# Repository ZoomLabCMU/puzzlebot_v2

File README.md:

# Configuration Control for Physical Coupling of Heterogeneous Robot Swarms
Sha Yi, Zeynep Temel, Katia Sycara

In this repo, we include the hardware design files and the code for our PuzzleBot configuration control project. This is based on the [original PuzzleBot repo](https://github.com/ZoomLab-CMU/puzzlebot). For more videos, please view [this](https://www.youtube.com/watch?v=vOY5iG4dra8). If you find our work useful, please consider citing our paper:  
```
@inproceedings{yi2022configuration,
  title={Configuration Control for Physical Coupling of Heterogeneous Robot Swarms},
  author={Yi, Sha and Temel, Zeynep and Sycara, Katia},
  booktitle={2022 IEEE International Conference on Robotics and Automation (ICRA)},
  year={2022},
  organization={IEEE}
}
```

## Preparation
### Hardware Setup
The hardware setup is the same as in the original [PuzzleBot setup](https://github.com/ZoomLab-CMU/puzzlebot). CAD files and circuit design files can be found in `files/`. The code for the circuit is `hardware_code/wifitcp_motor_only.ino`. Please modify the Wifi settings as [this](https://github.com/ZoomLab-CMU/puzzlebot).

### Software Setup
#### Simulation
Our simulation environment is based on [CoppeliaSim](https://www.coppeliarobotics.com/). The physics engine used is [Vortex Studio](https://www.cm-labs.com/vortex-studio/). Both the simulation and physics engine is free for educational use.  

Note that `Bullet` and `ODE` does not work for our concave robot body and will cause instability during contacts.  

Install the [ROS interface](https://www.coppeliarobotics.com/helpFiles/en/ros1Tutorial.htm) for _CoppeliaSim_.  

#### Packages
Basic ROS knowledge is required to run the demo. To build the ROS package, copy the repo into your ROS catkin source directory and build the package.

## Run the Demo in Simulation
1. Start `roscore`. Make sure the package is built in your catkin source directory.
2. Launch _CoppeliaSim_. Note that this should be ran after `roscore` to enable the ROS interface of the simulator.
3. Open the example simulation environment in `simulation/random_4.ttt`. Double check the _Vortex Studio_ is running properly.
4. Run the demo provided with 
```
rosrun puzzlebot_control run.py [NUMBER_OF_ROBOTS]
```
Note that if you would like to run different number of robots, you may also need to modify the target configuration parameters in [`src/puzzlebot_control/controller.py#L266`](src/puzzlebot_control/controller.py#L266).

## Run the Demo on Hardware Platform
Please follow the same procedure as in [this](https://github.com/ZoomLab-CMU/puzzlebot).

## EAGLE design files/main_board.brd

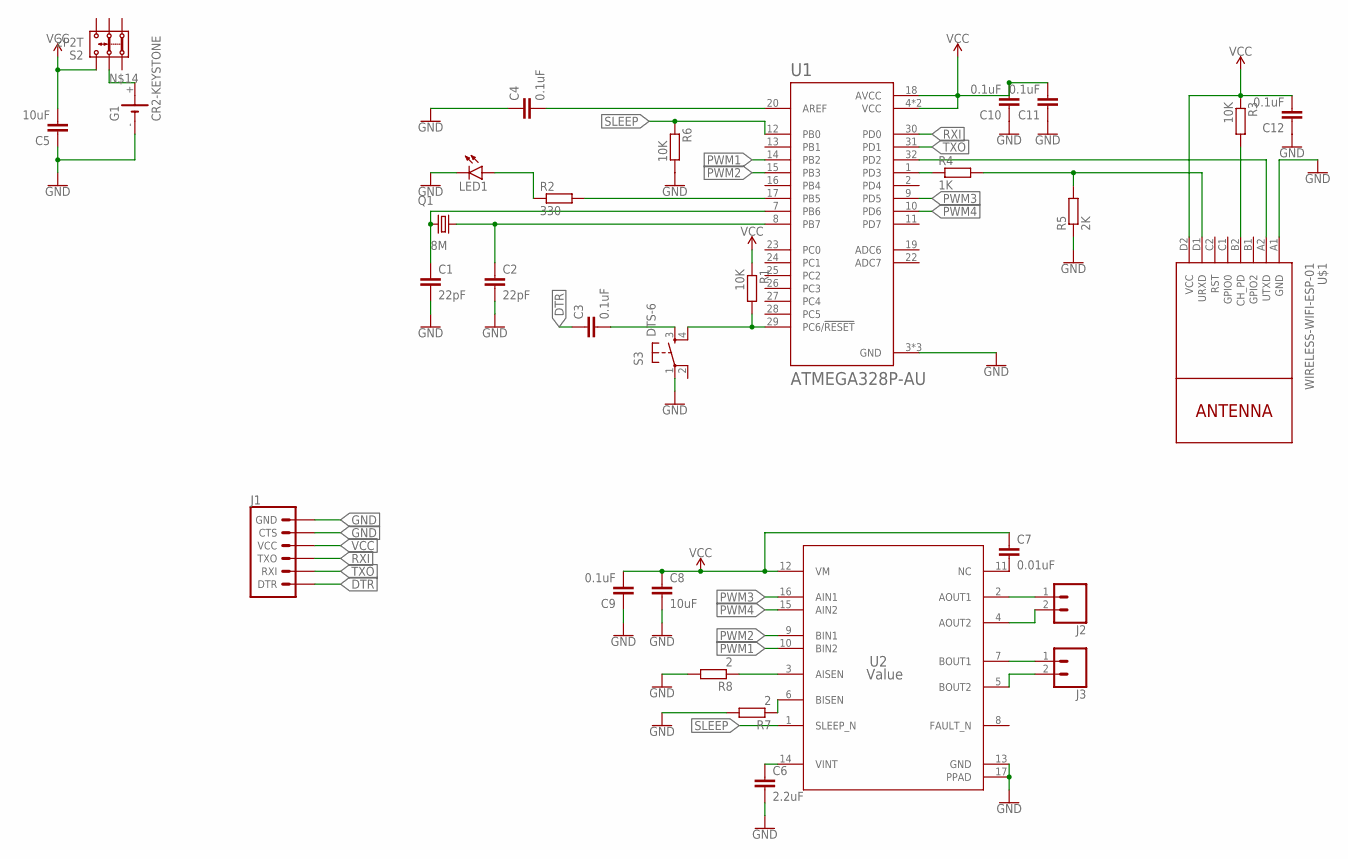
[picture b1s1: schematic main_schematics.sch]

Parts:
C1, C2: 22pF; C0603
C3, C4, C9, C10, C11, C12: 0.1uF; C0603
C5, C8: 10uF; C0603
C6: 2.2uF; C0603
C7: 0.01uF; C0603
G1: CR2-KEYSTONE; SL-150-1/2AA/PR
J1: 6_PIN_SERIAL_TARGETLONGPADS; 1X06_LONGPADS
J2, J3: CONN_02POLAR; MOLEX-1X2
LED1: LEDCHIP-LED0805; CHIP-LED0805
Q1: 8M; CSM-7X-DU
R1, R3, R6: 10K; R0603
R2: 330; R0603
R4: 1K; R0603
R5: 2K; R0603
R7, R8: 2; R0603
S2: 2P2T
S3: DTS-6
U1: ATMEGA328P-AU; QFP80P900X900X120-32N
U2: Value; PWP0016K_M
U$1: WIRELESS-WIFI-ESP-01

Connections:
DTR: C3.1, J1.1 (DTR)
GND: C1.2, C2.2, C4.1, C5.1, C6.2, C8.2, C9.1, C10.1, C11.1, C12.1, G1.-, J1.5 (CTS), J1.6 (GND), LED1.C, R5.1, R6.2, R7.2, R8.2, S3.1, U1.3 (GND), U1.5 (GND), U1.21 (GND), U2.13 (GND), U2.17 (PPAD), U$1.A1 (GND)
unnamed: C2.1, Q1.2, U1.8 (PB7)
unnamed: C1.1, Q1.1, U1.7 (PB6)
unnamed: C3.2, S3.3
unnamed: R1.2, S3.4, U1.29 (PC6/!RESET)
unnamed: R3.2, U$1.B2 (CH_PD)
unnamed: R2.2, U1.17 (PB5)
unnamed: LED1.A, R2.1
unnamed: C4.2, U1.20 (AREF)
unnamed: U1.32 (PD2), U$1.A2 (UTXD)
unnamed: R4.1, U1.1 (PD3)
unnamed: R4.2, R5.2, U$1.D1 (URXD)
unnamed: C6.1, U2.14 (VINT)
unnamed: C7.2, U2.11 (NC)
unnamed: G1.+, S2.2.1
unnamed: R7.1, U2.6 (BISEN)
unnamed: R8.1, U2.3 (AISEN)
unnamed: J2.1, U2.2 (AOUT1)
unnamed: J3.1, U2.7 (BOUT1)
unnamed: J2.2, U2.4 (AOUT2)
unnamed: J3.2, U2.5 (BOUT2)
PWM1: U1.14 (PB2), U2.10 (BIN2)
PWM2: U1.15 (PB3), U2.9 (BIN1)
PWM3: U1.9 (PD5), U2.16 (AIN1)
PWM4: U1.10 (PD6), U2.15 (AIN2)
RXI: J1.3 (TXO), U1.30 (PD0)
SLEEP: R6.1, U1.12 (PB0), U2.1 (SLEEP_N)
TXO: J1.2 (RXI), U1.31 (PD1)
VCC: C5.2, C7.1, C8.1, C9.2, C10.2, C11.2, C12.2, J1.4 (VCC), R1.1, R3.1, S2.3.1, U1.4 (VCC), U1.6 (VCC), U1.18 (AVCC), U2.12 (VM), U$1.D2 (VCC)

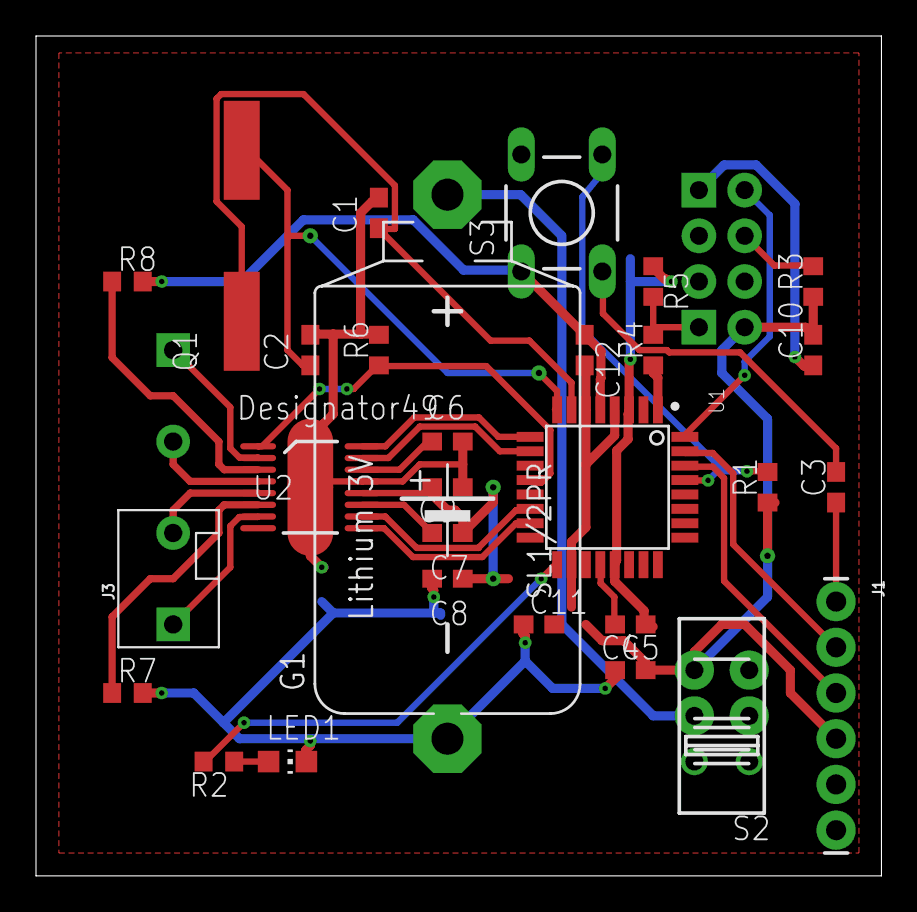
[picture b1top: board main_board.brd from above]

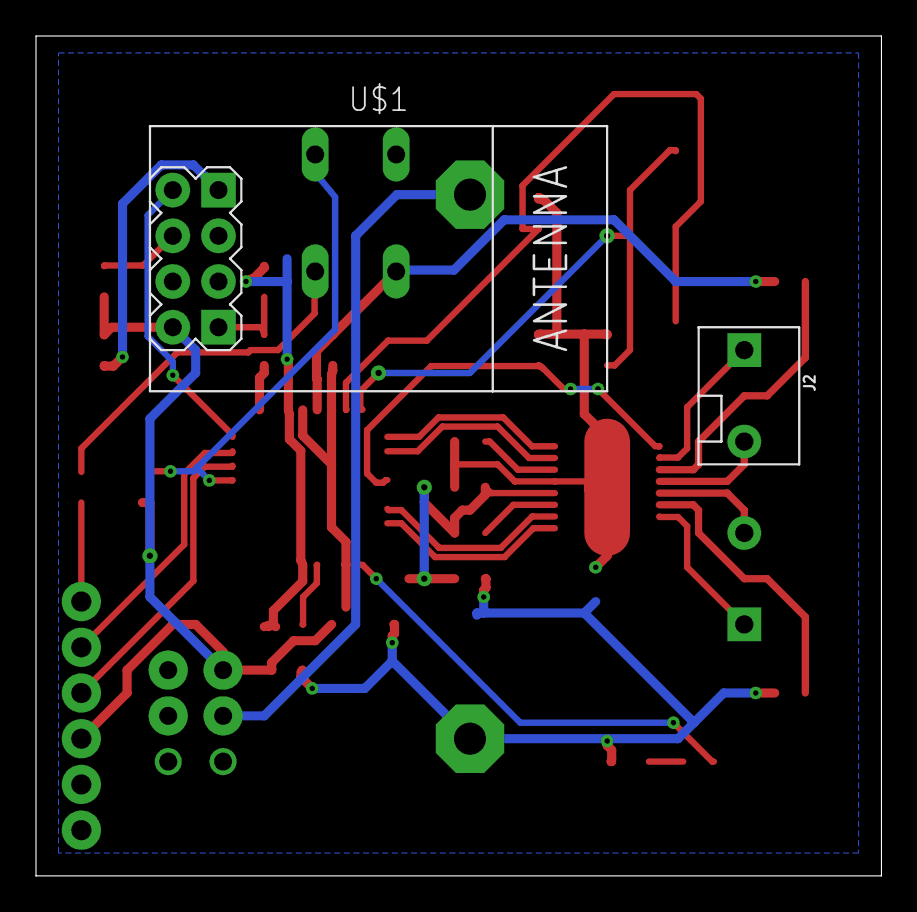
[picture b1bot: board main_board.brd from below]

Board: 2 copper layers, 47.0 x 46.7 mm, 31 parts (2 on the bottom side), 30 nets.

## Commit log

2022-02-28 init
2022-04-29 add hardware code
2022-04-30 add stl and boards

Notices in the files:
parts and their libraries:
SparkFun-Connectors: Licensing: Creative Commons ShareAlike 4.0 International - https://creativecommons.org/licenses/by-sa/4.0
diy-modules: Released under the Creative Commons Attribution 4.0 International License: http://creativecommons.org/licenses/by/4.0
